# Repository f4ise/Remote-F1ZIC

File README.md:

# Remote-F1ZIC
Systeme de telecommande du relais "Les Cloutons" F1ZIC

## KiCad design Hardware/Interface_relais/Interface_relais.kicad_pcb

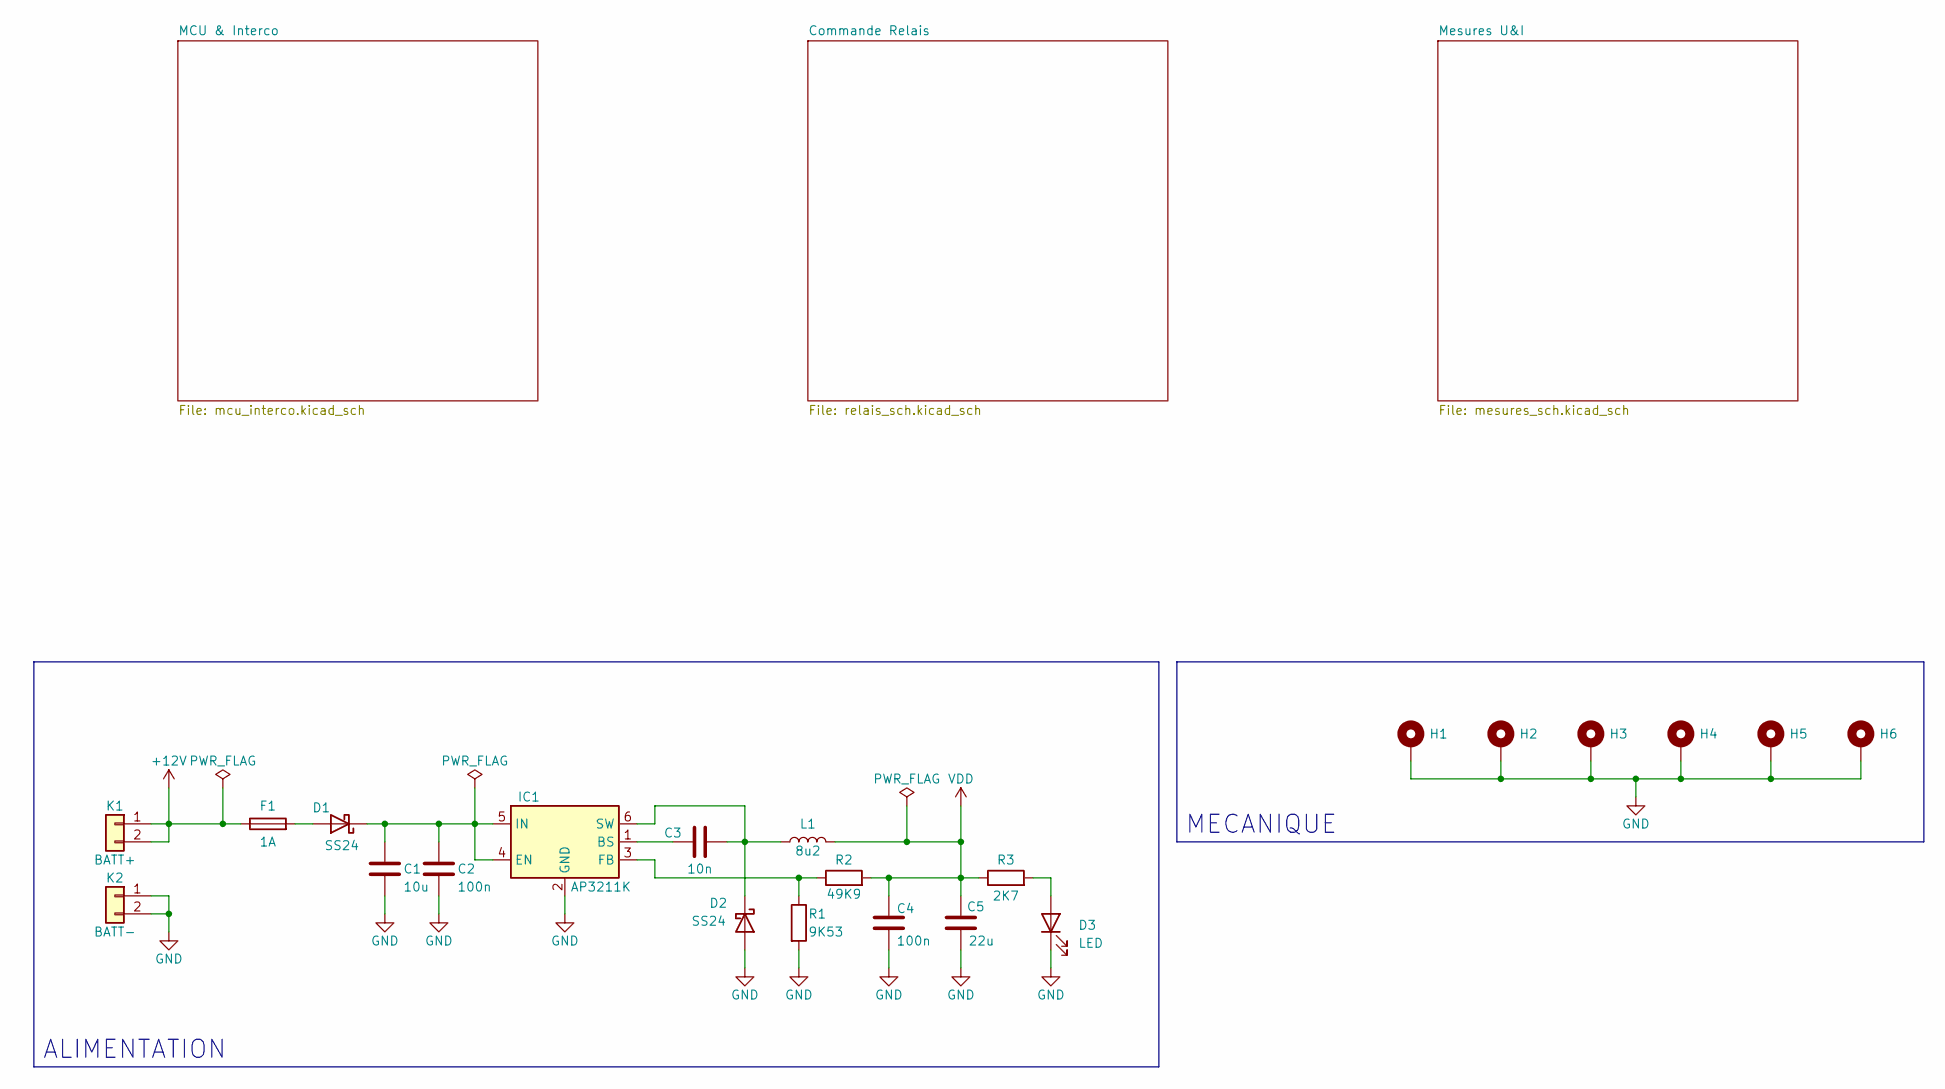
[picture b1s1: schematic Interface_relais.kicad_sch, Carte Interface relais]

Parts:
C1: 10u; C_0805_2012Metric
C2, C4: 100n; C_0603_1608Metric
C3: 10n; C_0603_1608Metric
C5: 22u; C_0805_2012Metric
D1, D2: SS24; D_SMB
D3: LED; LED_D3.0mm
F1: 1A; LITTELFUSE_178.6164.0001
H1, H2, H3, H4, H5, H6: MountingHole_Pad; MountingHole_3.2mm_M3_Pad_Via
IC1: AP3211K; SOT-23-6
K1: BATT+; TerminalBlock_Phoenix_MKDS-1,5-2-5.08_1x02_P5.08mm_Horizont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
K2: BATT-; TerminalBlock_Phoenix_MKDS-1,5-2-5.08_1x02_P5.08mm_Horizont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
L1: 8u2; L_Wuerth_WE-PD2-Typ-MS
R1: 9K53; R_0603_1608Metric
R2: 49K9; R_0603_1608Metric
R3: 2K7; R_0603_1608Metric

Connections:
+12V: F1.1, K1.1, K1.2; also elsewhere on the board
GND: C1.2, C2.2, C4.2, C5.2, D2.2 (A), D3.1 (K), H1.1, H2.1, H3.1, H4.1, H5.1, H6.1, IC1.2 (GND), K2.1, K2.2, R1.2; also elsewhere on the board
unnamed: D1.2 (A), F1.2
unnamed: C1.1, C2.1, D1.1 (K), IC1.4 (EN), IC1.5 (IN)
unnamed: C3.2, D2.1 (K), IC1.6 (SW), L1.1
unnamed: D3.2 (A), R3.2
unnamed: C3.1, IC1.1 (BS)
unnamed: IC1.3 (FB), R1.1, R2.1
VDD: C4.1, C5.1, L1.2, R2.2, R3.1; also elsewhere on the board

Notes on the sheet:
ALIMENTATION
MECANIQUE

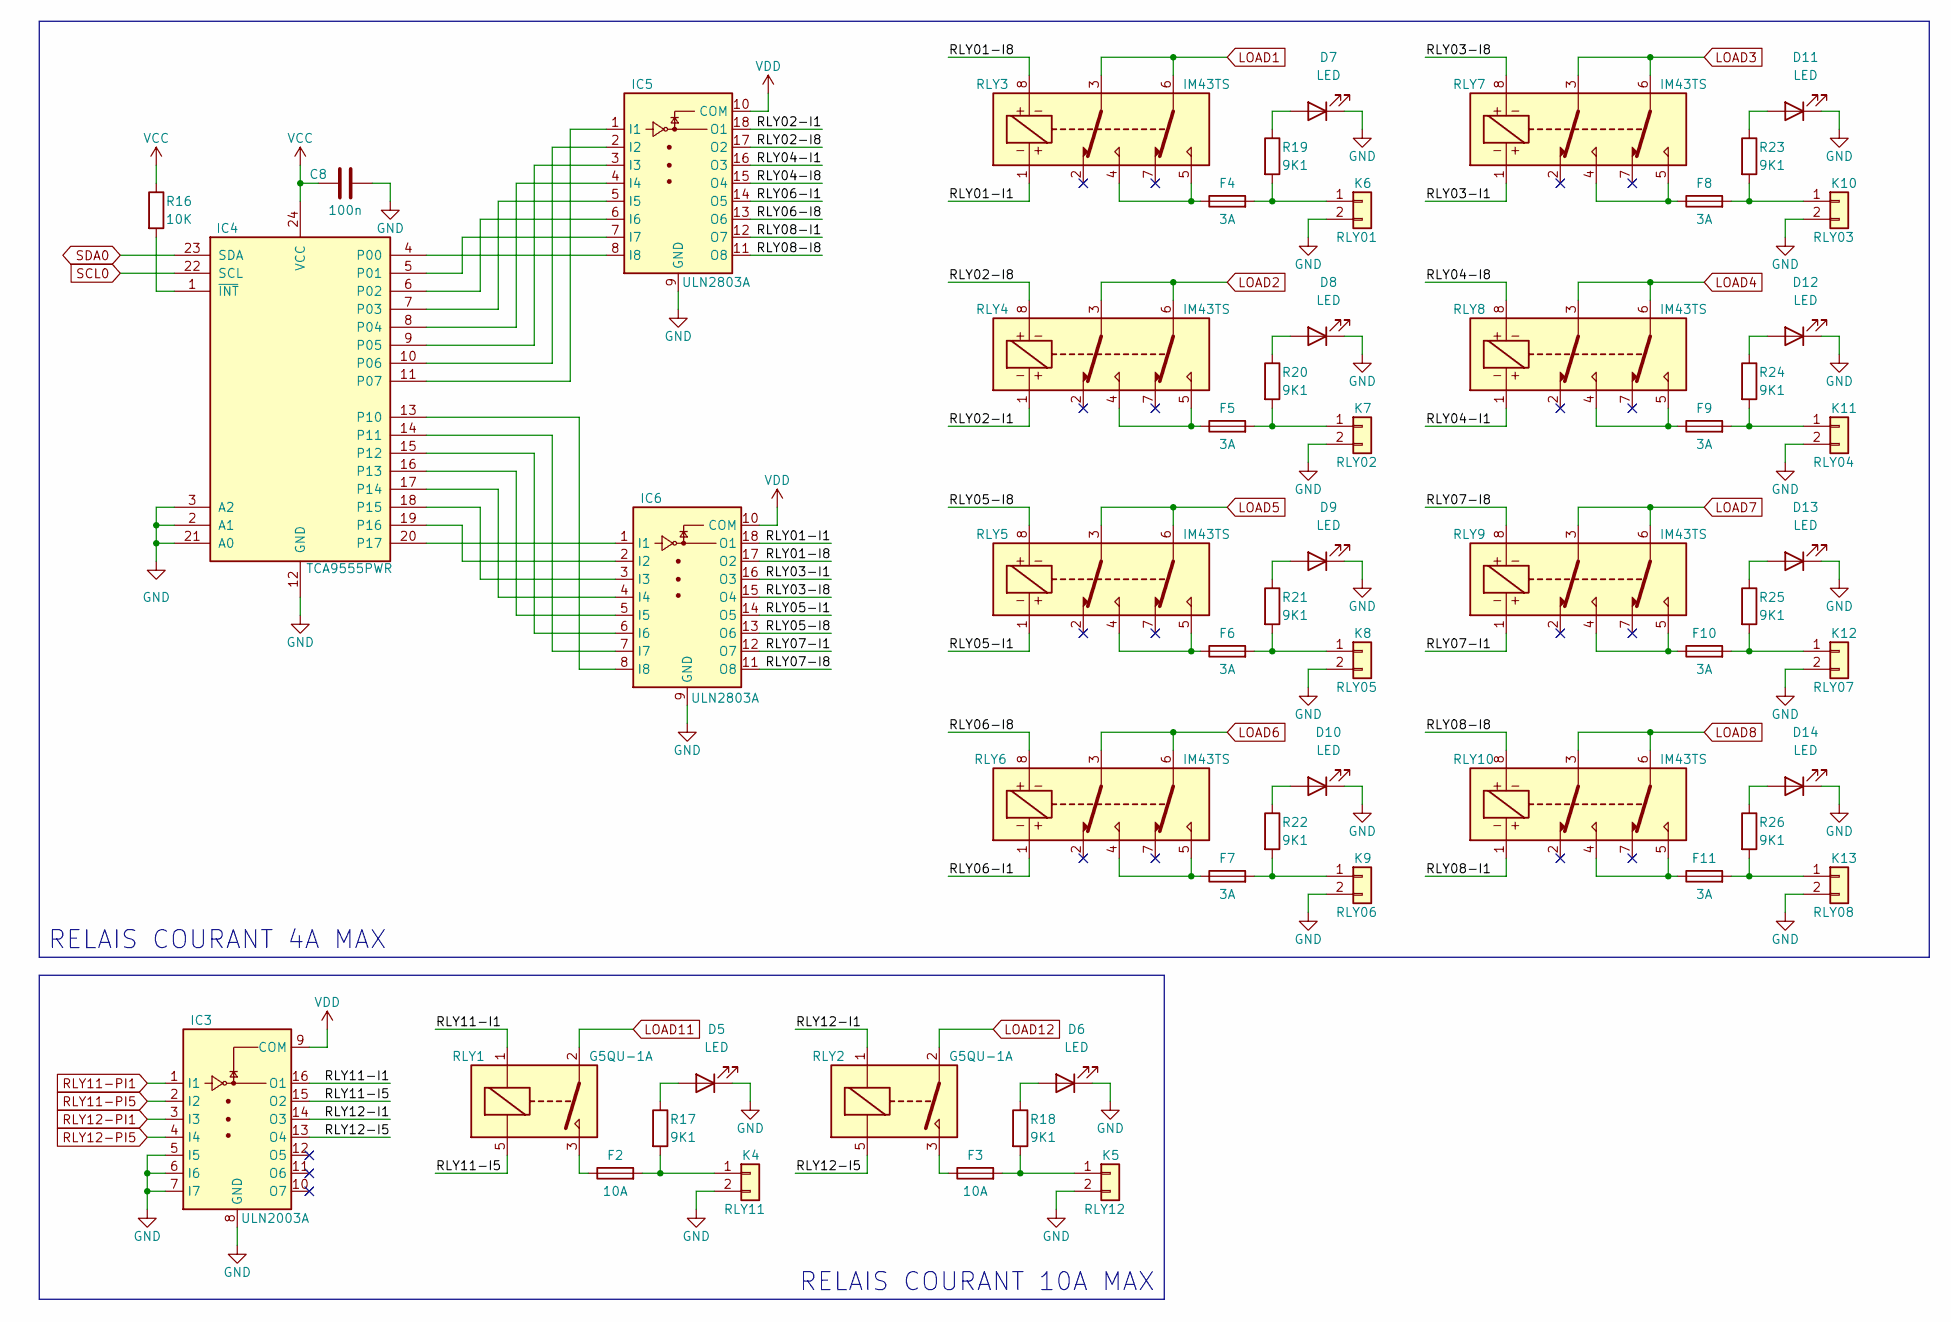
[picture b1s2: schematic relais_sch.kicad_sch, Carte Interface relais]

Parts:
C8: 100n; C_0603_1608Metric
D5, D6, D7, D8, D9, D10, D11, D12, D13, D14: LED; LED_D3.0mm
F2, F3: 10A; LITTELFUSE_178.6164.0001
F4, F5, F6, F7, F8, F9, F10, F11: 3A; LITTELFUSE_178.6164.0001
IC3: ULN2003A; SO-16_5.3x10.2mm_P1.27mm
IC4: TCA9555PWR; TSSOP-24_4.4x7.8mm_P0.65mm
IC5, IC6: ULN2803A; SOIC-18W_7.5x11.6mm_P1.27mm
K4: RLY11; TerminalBlock_Phoenix_MKDS-1,5-2-5.08_1x02_P5.08mm_Horizont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
K5: RLY12; TerminalBlock_Phoenix_MKDS-1,5-2-5.08_1x02_P5.08mm_Horizont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
K6: RLY01; TerminalBlock_Phoenix_MKDS-1,5-2-5.08_1x02_P5.08mm_Horizont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
K7: RLY02; TerminalBlock_Phoenix_MKDS-1,5-2-5.08_1x02_P5.08mm_Horizont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
K8: RLY05; TerminalBlock_Phoenix_MKDS-1,5-2-5.08_1x02_P5.08mm_Horizont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
K9: RLY06; TerminalBlock_Phoenix_MKDS-1,5-2-5.08_1x02_P5.08mm_Horizont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
K10: RLY03; TerminalBlock_Phoenix_MKDS-1,5-2-5.08_1x02_P5.08mm_Horizont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
K11: RLY04; TerminalBlock_Phoenix_MKDS-1,5-2-5.08_1x02_P5.08mm_Horizont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
K12: RLY07; TerminalBlock_Phoenix_MKDS-1,5-2-5.08_1x02_P5.08mm_Horizont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
K13: RLY08; TerminalBlock_Phoenix_MKDS-1,5-2-5.08_1x02_P5.08mm_Horizont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
R16: 10K; R_0603_1608Metric
R17, R18, R19, R20, R21, R22, R23, R24, R25, R26: 9K1; R_0603_1608Metric
RLY1, RLY2: G5QU-1A; Relay_SPST_Omron-G5Q-1A
RLY3, RLY4, RLY5, RLY6, RLY7, RLY8, RLY9, RLY10: IM43TS; Relay_DPDT_AXICOM_IMSeries_Pitch5.08mm

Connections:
/Commande Relais/RLY01-I1: IC6.18 (O1), RLY3.1
/Commande Relais/RLY01-I8: IC6.17 (O2), RLY3.8
/Commande Relais/RLY02-I1: IC5.18 (O1), RLY4.1
/Commande Relais/RLY02-I8: IC5.17 (O2), RLY4.8
/Commande Relais/RLY03-I1: IC6.16 (O3), RLY7.1
/Commande Relais/RLY03-I8: IC6.15 (O4), RLY7.8
/Commande Relais/RLY04-I1: IC5.16 (O3), RLY8.1
/Commande Relais/RLY04-I8: IC5.15 (O4), RLY8.8
/Commande Relais/RLY05-I1: IC6.14 (O5), RLY5.1
/Commande Relais/RLY05-I8: IC6.13 (O6), RLY5.8
/Commande Relais/RLY06-I1: IC5.14 (O5), RLY6.1
/Commande Relais/RLY06-I8: IC5.13 (O6), RLY6.8
/Commande Relais/RLY07-I1: IC6.12 (O7), RLY9.1
/Commande Relais/RLY07-I8: IC6.11 (O8), RLY9.8
/Commande Relais/RLY08-I1: IC5.12 (O7), RLY10.1
/Commande Relais/RLY08-I8: IC5.11 (O8), RLY10.8
/Commande Relais/RLY11-I1: IC3.16 (O1), RLY1.1
/Commande Relais/RLY11-I5: IC3.15 (O2), RLY1.5
/Commande Relais/RLY12-I1: IC3.14 (O3), RLY2.1
/Commande Relais/RLY12-I5: IC3.13 (O4), RLY2.5
GND: C8.2, D5.1 (K), D6.1 (K), D7.1 (K), D8.1 (K), D9.1 (K), D10.1 (K), D11.1 (K), D12.1 (K), D13.1 (K), D14.1 (K), IC3.5 (I5), IC3.6 (I6), IC3.7 (I7), IC3.8 (GND), IC4.2 (A1), IC4.3 (A2), IC4.12 (GND), IC4.21 (A0), IC5.9 (GND), IC6.9 (GND), K4.2, K5.2, K6.2, K7.2, K8.2, K9.2, K10.2, K11.2, K12.2, K13.2; also elsewhere on the board
LOAD1: RLY3.3, RLY3.6; also elsewhere on the board
LOAD2: RLY4.3, RLY4.6; also elsewhere on the board
LOAD3: RLY7.3, RLY7.6; also elsewhere on the board
LOAD4: RLY8.3, RLY8.6; also elsewhere on the board
LOAD5: RLY5.3, RLY5.6; also elsewhere on the board
LOAD6: RLY6.3, RLY6.6; also elsewhere on the board
LOAD7: RLY9.3, RLY9.6; also elsewhere on the board
LOAD8: RLY10.3, RLY10.6; also elsewhere on the board
LOAD11: RLY1.2; also elsewhere on the board
LOAD12: RLY2.2; also elsewhere on the board
unnamed: D5.2 (A), R17.1
unnamed: D6.2 (A), R18.1
unnamed: D7.2 (A), R19.1
unnamed: D8.2 (A), R20.1
unnamed: D9.2 (A), R21.1
unnamed: D10.2 (A), R22.1
unnamed: D11.2 (A), R23.1
unnamed: D12.2 (A), R24.1
unnamed: D13.2 (A), R25.1
unnamed: D14.2 (A), R26.1
unnamed: F2.1, RLY1.3
unnamed: F3.1, RLY2.3
unnamed: F4.1, RLY3.4, RLY3.5
unnamed: F5.1, RLY4.4, RLY4.5
unnamed: F6.1, RLY5.4, RLY5.5
unnamed: F7.1, RLY6.4, RLY6.5
unnamed: F8.1, RLY7.4, RLY7.5
unnamed: F9.1, RLY8.4, RLY8.5
unnamed: F10.1, RLY9.4, RLY9.5
unnamed: F11.1, RLY10.4, RLY10.5
unnamed: IC4.4 (P00), IC5.8 (I8)
unnamed: IC4.5 (P01), IC5.7 (I7)
unnamed: IC4.6 (P02), IC5.6 (I6)
unnamed: IC4.7 (P03), IC5.5 (I5)
unnamed: IC4.8 (P04), IC5.4 (I4)
unnamed: IC4.9 (P05), IC5.3 (I3)
unnamed: IC4.10 (P06), IC5.2 (I2)
unnamed: IC4.11 (P07), IC5.1 (I1)
unnamed: IC4.13 (P10), IC6.8 (I8)
unnamed: IC4.14 (P11), IC6.7 (I7)
unnamed: IC4.15 (P12), IC6.6 (I6)
unnamed: IC4.16 (P13), IC6.5 (I5)
unnamed: IC4.17 (P14), IC6.4 (I4)
unnamed: IC4.18 (P15), IC6.3 (I3)
unnamed: IC4.19 (P16), IC6.2 (I2)
unnamed: IC4.20 (P17), IC6.1 (I1)
unnamed: IC4.1 (~INT), R16.2
unnamed: F2.2, K4.1, R17.2
unnamed: F3.2, K5.1, R18.2
unnamed: F4.2, K6.1, R19.2
unnamed: F5.2, K7.1, R20.2
unnamed: F6.2, K8.1, R21.2
unnamed: F7.2, K9.1, R22.2
unnamed: F8.2, K10.1, R23.2
unnamed: F9.2, K11.1, R24.2
unnamed: F10.2, K12.1, R25.2
unnamed: F11.2, K13.1, R26.2
RLY11-PI1: IC3.1 (I1); also elsewhere on the board
RLY11-PI5: IC3.2 (I2); also elsewhere on the board
RLY12-PI1: IC3.3 (I3); also elsewhere on the board
RLY12-PI5: IC3.4 (I4); also elsewhere on the board
SCL0: IC4.22 (SCL); also elsewhere on the board
SDA0: IC4.23 (SDA); also elsewhere on the board
VCC: C8.1, IC4.24 (VCC), R16.1; also elsewhere on the board
VDD: IC3.9 (COM), IC5.10 (COM), IC6.10 (COM); also elsewhere on the board

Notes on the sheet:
RELAIS COURANT 4A MAX
RELAIS COURANT 10A MAX

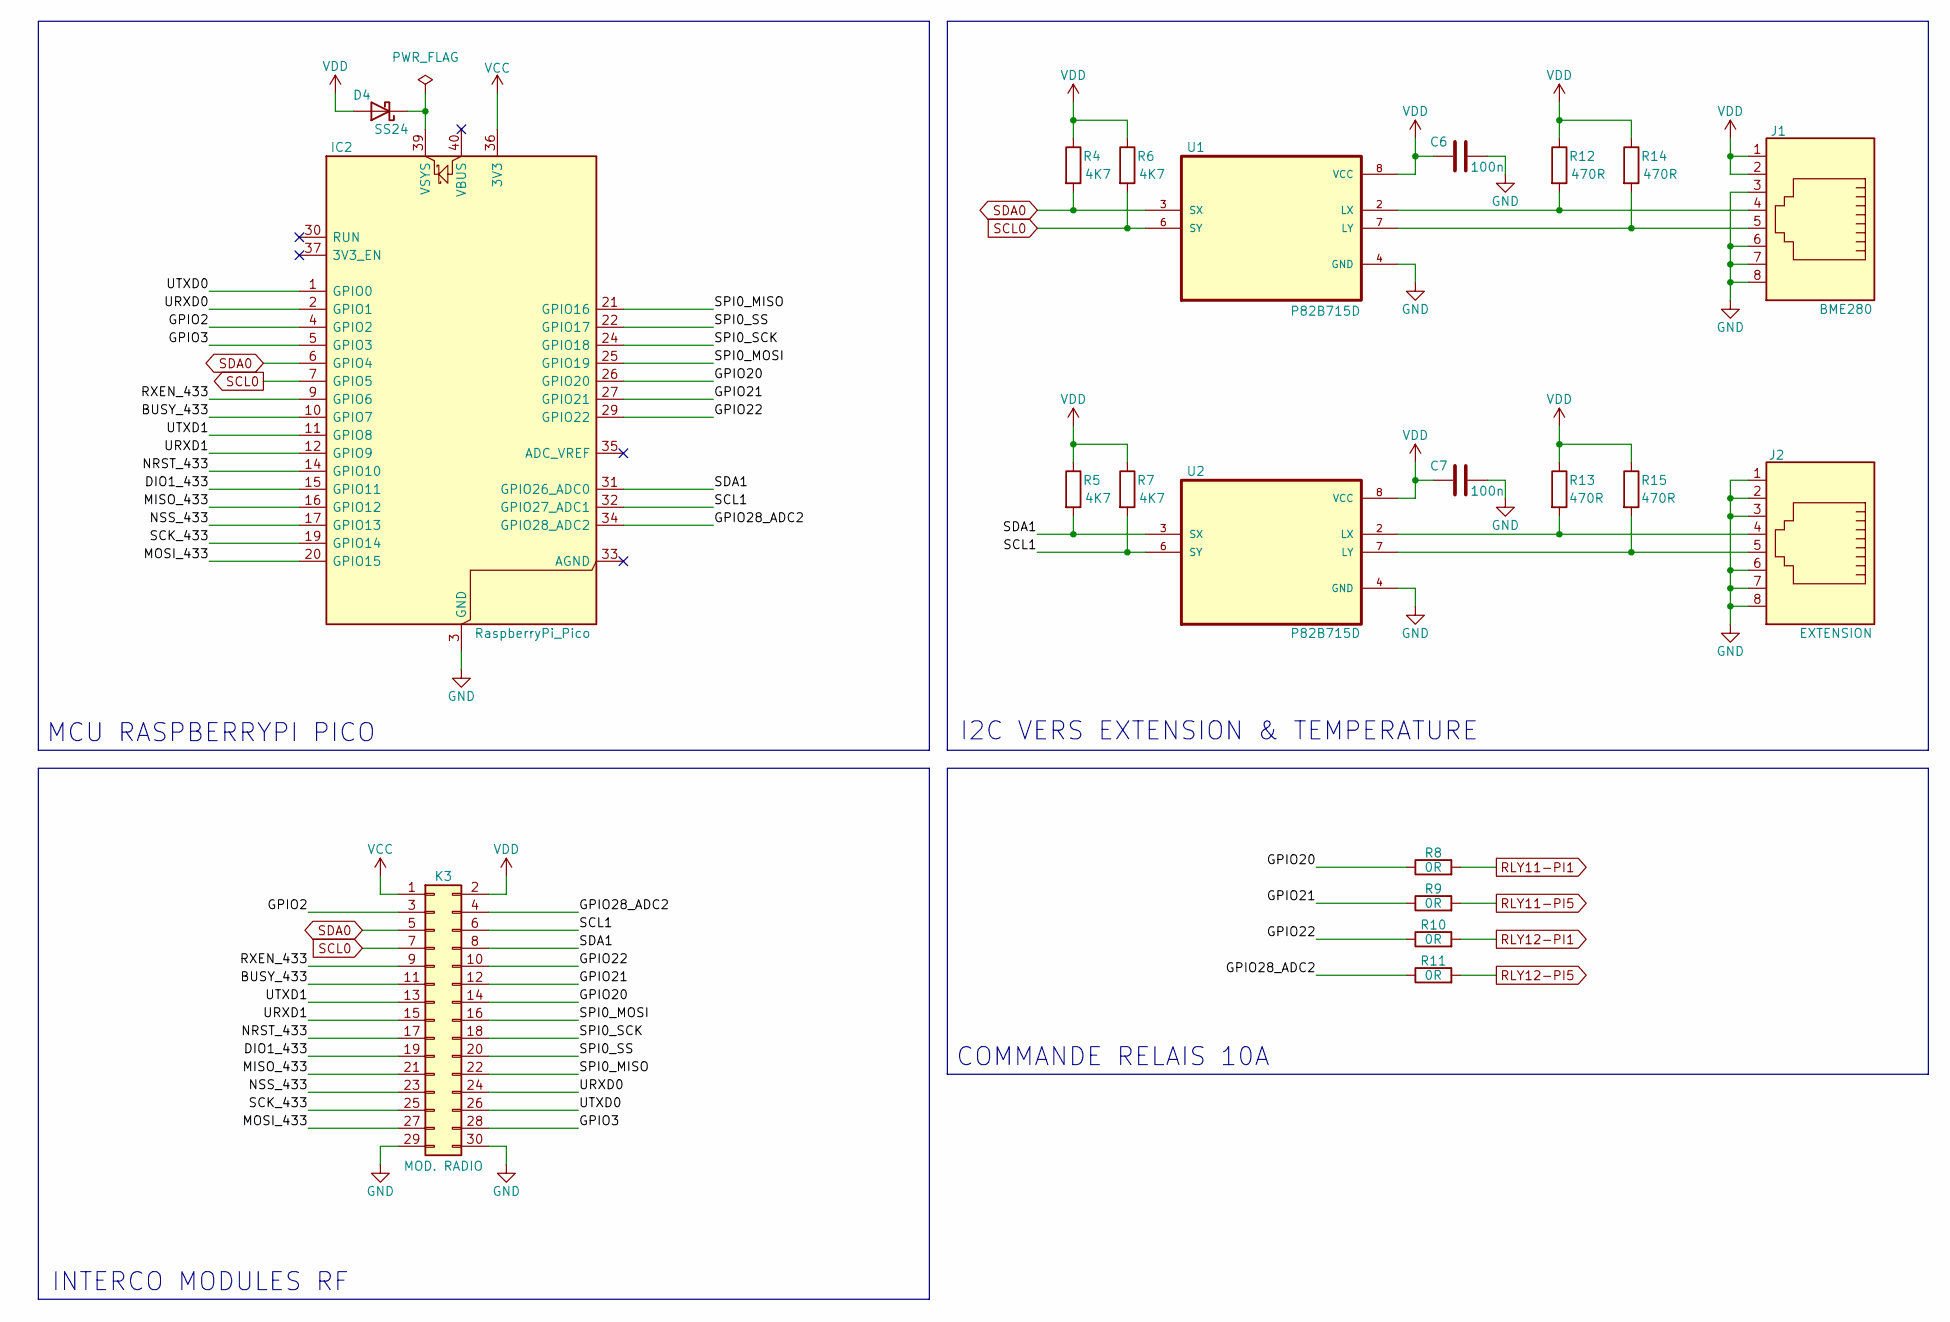
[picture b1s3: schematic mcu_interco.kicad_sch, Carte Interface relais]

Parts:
C6, C7: 100n; C_0603_1608Metric
D4: SS24; D_SMB
IC2: RaspberryPi_Pico; RaspberryPi_Pico_Common_Unspecified
J1: BME280; RJ45_Amphenol_54602-x08_Horizontal
J2: EXTENSION; RJ45_Amphenol_54602-x08_Horizontal
K3: MOD. RADIO; PinHeader_2x15_P2.54mm_Vertical
R4, R5, R6, R7: 4K7; R_0603_1608Metric
R8, R9, R10, R11: 0R; R_0603_1608Metric
R12, R13, R14, R15: 470R; R_0603_1608Metric
U1, U2: P82B715D; SOIC127P599X175-8N

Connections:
/MCU & Interco/BUSY_433: IC2.10 (GPIO7), K3.11
/MCU & Interco/DIO1_433: IC2.15 (GPIO11), K3.19
/MCU & Interco/GPIO2: IC2.4 (GPIO2), K3.3
/MCU & Interco/GPIO3: IC2.5 (GPIO3), K3.28
/MCU & Interco/GPIO20: IC2.26 (GPIO20), K3.14, R8.1
/MCU & Interco/GPIO21: IC2.27 (GPIO21), K3.12, R9.1
/MCU & Interco/GPIO22: IC2.29 (GPIO22), K3.10, R10.1
/MCU & Interco/GPIO28_ADC2: IC2.34 (GPIO28_ADC2), K3.4, R11.1
/MCU & Interco/MISO_433: IC2.16 (GPIO12), K3.21
/MCU & Interco/MOSI_433: IC2.20 (GPIO15), K3.27
/MCU & Interco/NRST_433: IC2.14 (GPIO10), K3.17
/MCU & Interco/NSS_433: IC2.17 (GPIO13), K3.23
/MCU & Interco/RXEN_433: IC2.9 (GPIO6), K3.9
/MCU & Interco/SCK_433: IC2.19 (GPIO14), K3.25
/MCU & Interco/SCL1: IC2.32 (GPIO27_ADC1), K3.6, R7.2, U2.6 (SY)
/MCU & Interco/SDA1: IC2.31 (GPIO26_ADC0), K3.8, R5.2, U2.3 (SX)
/MCU & Interco/SPI0_MISO: IC2.21 (GPIO16), K3.22
/MCU & Interco/SPI0_MOSI: IC2.25 (GPIO19), K3.16
/MCU & Interco/SPI0_SCK: IC2.24 (GPIO18), K3.18
/MCU & Interco/SPI0_SS: IC2.22 (GPIO17), K3.20
/MCU & Interco/URXD0: IC2.2 (GPIO1), K3.24
/MCU & Interco/URXD1: IC2.12 (GPIO9), K3.15
/MCU & Interco/UTXD0: IC2.1 (GPIO0), K3.26
/MCU & Interco/UTXD1: IC2.11 (GPIO8), K3.13
GND: C6.2, C7.2, IC2.3 (GND), IC2.8 (GND), IC2.13 (GND), IC2.18 (GND), IC2.23 (GND), IC2.28 (GND), IC2.38 (GND), J1.3, J1.6, J1.7, J1.8, J2.1, J2.2, J2.3, J2.6, J2.7, J2.8, K3.29, K3.30, U1.4 (GND), U2.4 (GND); also elsewhere on the board
unnamed: D4.1 (K), IC2.39 (VSYS)
unnamed: J1.4, R12.2, U1.2 (LX)
unnamed: J1.5, R14.2, U1.7 (LY)
unnamed: J2.4, R13.2, U2.2 (LX)
unnamed: J2.5, R15.2, U2.7 (LY)
RLY11-PI1: R8.2; also elsewhere on the board
RLY11-PI5: R9.2; also elsewhere on the board
RLY12-PI1: R10.2; also elsewhere on the board
RLY12-PI5: R11.2; also elsewhere on the board
SCL0: IC2.7 (GPIO5), K3.7, R6.2, U1.6 (SY); also elsewhere on the board
SDA0: IC2.6 (GPIO4), K3.5, R4.2, U1.3 (SX); also elsewhere on the board
VCC: IC2.36 (3V3), K3.1; also elsewhere on the board
VDD: C6.1, C7.1, D4.2 (A), J1.1, J1.2, K3.2, R4.1, R5.1, R6.1, R7.1, R12.1, R13.1, R14.1, R15.1, U1.8 (VCC), U2.8 (VCC); also elsewhere on the board

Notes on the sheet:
I2C VERS EXTENSION & TEMPERATURE
INTERCO MODULES RF
COMMANDE RELAIS 10A
MCU RASPBERRYPI PICO

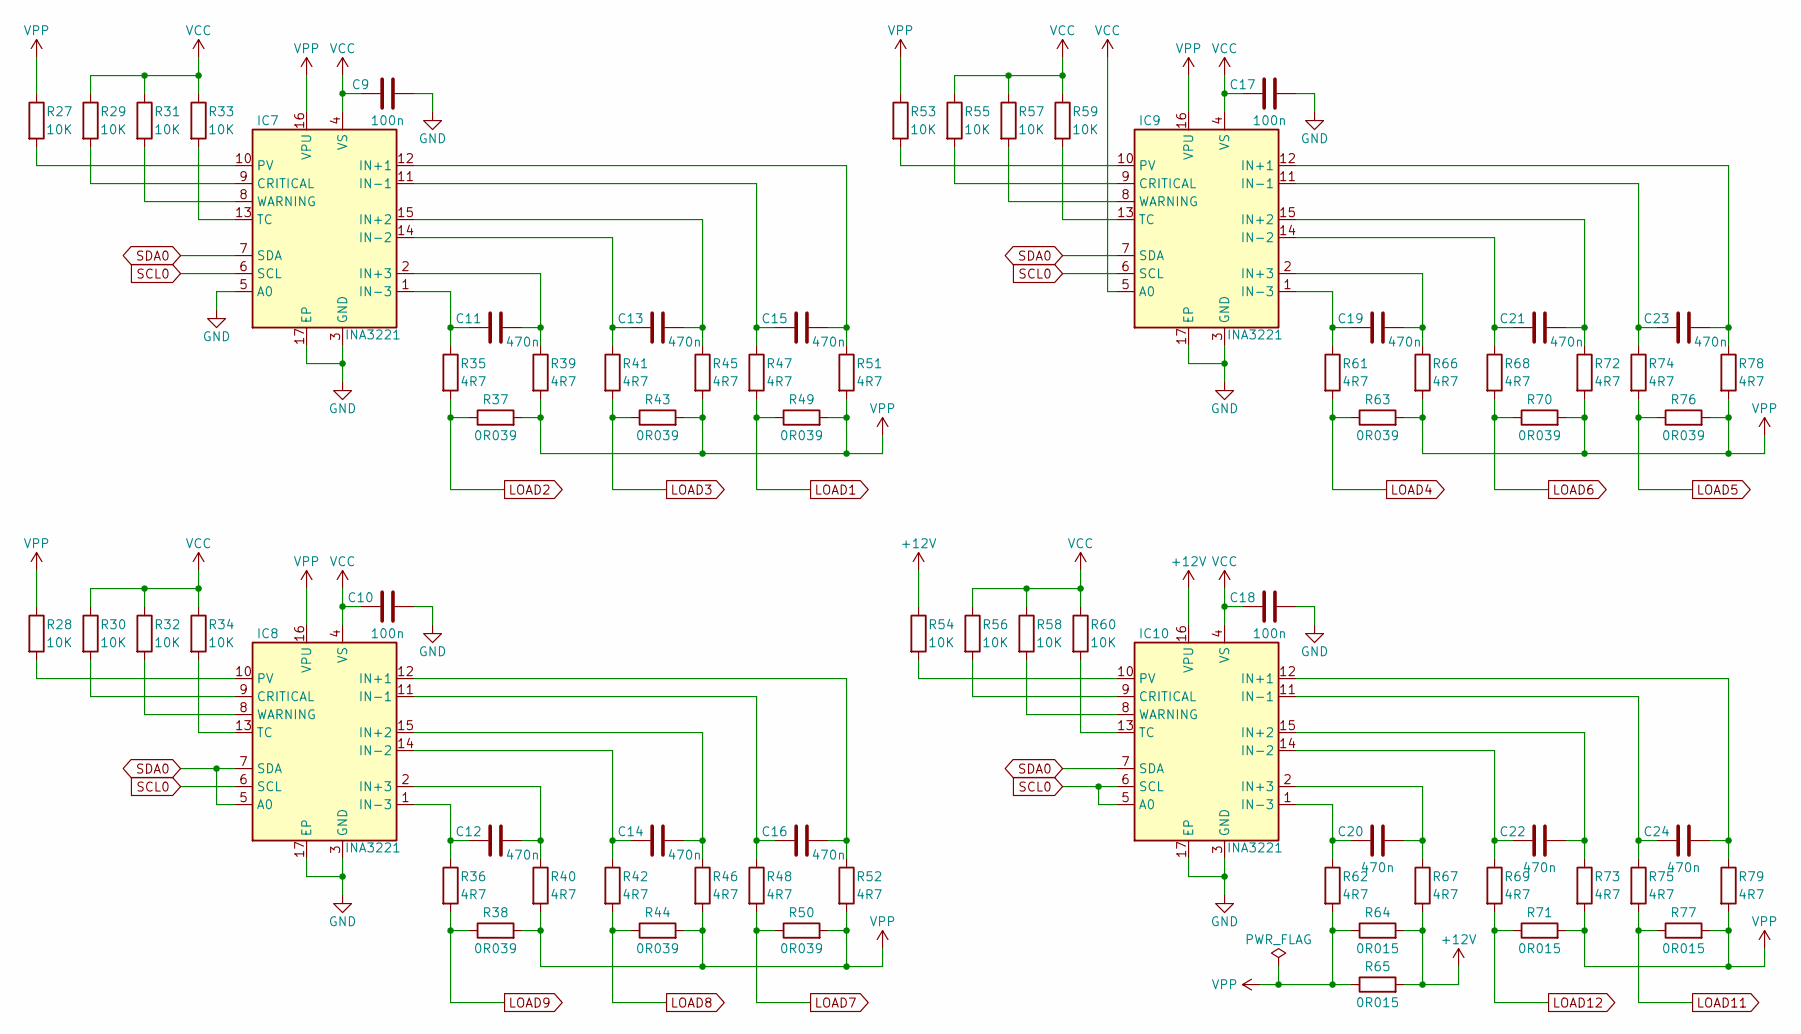
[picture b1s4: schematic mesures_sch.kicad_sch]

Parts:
C9, C10, C17, C18: 100n; C_0603_1608Metric
C11, C12, C13, C14, C15, C16, C19, C20, C21, C22, C23, C24: 470n; C_0603_1608Metric
IC7, IC8, IC9, IC10: INA3221; Texas_RGV0016A_VQFN-16-1EP_4x4mm_P0.65mm_EP2.1x2.1mm
R27, R28, R29, R30, R31, R32, R33, R34, R53, R54, R55, R56, R57, R58, R59, R60: 10K; R_0603_1608Metric
R35, R36, R39, R40, R41, R42, R45, R46, R47, R48, R51, R52, R61, R62, R66, R67, R68, R69, R72, R73, R74, R75, R78, R79: 4R7; R_0603_1608Metric
R37, R38, R43, R44, R49, R50, R63, R70, R76: 0R039; R_1206_3216Metric
R64, R65, R71, R77: 0R015; R_1206_3216Metric

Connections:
+12V: IC10.16 (VPU), R54.1, R64.2, R65.2, R67.2; also elsewhere on the board
GND: C9.2, C10.2, C17.2, C18.2, IC7.3 (GND), IC7.5 (A0), IC7.17 (EP), IC8.3 (GND), IC8.17 (EP), IC9.3 (GND), IC9.17 (EP), IC10.3 (GND), IC10.17 (EP); also elsewhere on the board
LOAD1: R47.2, R49.1; also elsewhere on the board
LOAD2: R35.2, R37.1; also elsewhere on the board
LOAD3: R41.2, R43.1; also elsewhere on the board
LOAD4: R61.2, R63.1; also elsewhere on the board
LOAD5: R74.2, R76.1; also elsewhere on the board
LOAD6: R68.2, R70.1; also elsewhere on the board
LOAD7: R48.2, R50.1; also elsewhere on the board
LOAD8: R42.2, R44.1; also elsewhere on the board
LOAD9: R36.2, R38.1
LOAD11: R75.2, R77.1; also elsewhere on the board
LOAD12: R69.2, R71.1; also elsewhere on the board
unnamed: IC7.9 (CRITICAL), R29.2
unnamed: C15.2, IC7.12 (IN+1), R51.1
unnamed: C13.2, IC7.15 (IN+2), R45.1
unnamed: C11.2, IC7.2 (IN+3), R39.1
unnamed: C15.1, IC7.11 (IN-1), R47.1
unnamed: C13.1, IC7.14 (IN-2), R41.1
unnamed: C11.1, IC7.1 (IN-3), R35.1
unnamed: IC7.10 (PV), R27.2
unnamed: IC7.13 (TC), R33.2
unnamed: IC7.8 (WARNING), R31.2
unnamed: IC8.9 (CRITICAL), R30.2
unnamed: C16.2, IC8.12 (IN+1), R52.1
unnamed: C14.2, IC8.15 (IN+2), R46.1
unnamed: C12.2, IC8.2 (IN+3), R40.1
unnamed: C16.1, IC8.11 (IN-1), R48.1
unnamed: C14.1, IC8.14 (IN-2), R42.1
unnamed: C12.1, IC8.1 (IN-3), R36.1
unnamed: IC8.10 (PV), R28.2
unnamed: IC8.13 (TC), R34.2
unnamed: IC8.8 (WARNING), R32.2
unnamed: IC9.9 (CRITICAL), R55.2
unnamed: C23.2, IC9.12 (IN+1), R78.1
unnamed: C21.2, IC9.15 (IN+2), R72.1
unnamed: C19.2, IC9.2 (IN+3), R66.1
unnamed: C23.1, IC9.11 (IN-1), R74.1
unnamed: C21.1, IC9.14 (IN-2), R68.1
unnamed: C19.1, IC9.1 (IN-3), R61.1
unnamed: IC9.10 (PV), R53.2
unnamed: IC9.13 (TC), R59.2
unnamed: IC9.8 (WARNING), R57.2
unnamed: IC10.9 (CRITICAL), R56.2
unnamed: C24.2, IC10.12 (IN+1), R79.1
unnamed: C22.2, IC10.15 (IN+2), R73.1
unnamed: C20.2, IC10.2 (IN+3), R67.1
unnamed: C24.1, IC10.11 (IN-1), R75.1
unnamed: C22.1, IC10.14 (IN-2), R69.1
unnamed: C20.1, IC10.1 (IN-3), R62.1
unnamed: IC10.10 (PV), R54.2
unnamed: IC10.13 (TC), R60.2
unnamed: IC10.8 (WARNING), R58.2
SCL0: IC7.6 (SCL), IC8.6 (SCL), IC9.6 (SCL), IC10.5 (A0), IC10.6 (SCL); also elsewhere on the board
SDA0: IC7.7 (SDA), IC8.5 (A0), IC8.7 (SDA), IC9.7 (SDA), IC10.7 (SDA); also elsewhere on the board
VCC: C9.1, C10.1, C17.1, C18.1, IC7.4 (VS), IC8.4 (VS), IC9.4 (VS), IC9.5 (A0), IC10.4 (VS), R29.1, R30.1, R31.1, R32.1, R33.1, R34.1, R55.1, R56.1, R57.1, R58.1, R59.1, R60.1; also elsewhere on the board
VPP: IC7.16 (VPU), IC8.16 (VPU), IC9.16 (VPU), R27.1, R28.1, R37.2, R38.2, R39.2, R40.2, R43.2, R44.2, R45.2, R46.2, R49.2, R50.2, R51.2, R52.2, R53.1, R62.2, R63.2, R64.1, R65.1, R66.2, R70.2, R71.2, R72.2, R73.2, R76.2, R77.2, R78.2, R79.2

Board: 4 copper layers, 172 parts (118 on the bottom side), 164 nets, no tracks yet.

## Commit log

2025-10-07 WIP Interface relais
2025-11-20 Add WIP Weatherino
